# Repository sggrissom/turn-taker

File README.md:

# Turn Taker - RP2040 + SSD1315 OLED Project

A Raspberry Pi Pico project with SSD1315/SSD1306 I2C OLED display support.

## Prerequisites

1. **Pico SDK** - Install the Raspberry Pi Pico SDK:
   ```bash
   git clone https://github.com/raspberrypi/pico-sdk.git
   cd pico-sdk
   git submodule update --init
   export PICO_SDK_PATH=$(pwd)
   ```

2. **ARM Toolchain**:
   ```bash
   # Arch Linux
   sudo pacman -S arm-none-eabi-gcc arm-none-eabi-newlib

   # Ubuntu/Debian
   sudo apt install gcc-arm-none-eabi libnewlib-arm-none-eabi
   ```

3. **CMake** (version 3.13+):
   ```bash
   # Arch Linux
   sudo pacman -S cmake

   # Ubuntu/Debian
   sudo apt install cmake
   ```

## Wiring

Connect the SSD1315 OLED display to the Pico:

| Pico Pin | GPIO | Display Pin | Description  |
|----------|------|-------------|--------------|
| 6        | GP4  | SDA         | I2C Data     |
| 7        | GP5  | SCL         | I2C Clock    |
| 36       | 3V3  | VCC         | Power (3.3V) |
| 38       | GND  | GND         | Ground       |

```
         ┌─────────────────┐
         │  Raspberry Pi   │
         │      Pico       │
         │                 │
    SDA ─┤ GP4 (pin 6)     │
    SCL ─┤ GP5 (pin 7)     │
    VCC ─┤ 3V3 (pin 36)    │
    GND ─┤ GND (pin 38)    │
         └─────────────────┘
```

## Building

1. Set the SDK path (if not already set):
   ```bash
   export PICO_SDK_PATH=/path/to/pico-sdk
   ```

2. Create build directory and compile:
   ```bash
   mkdir build && cd build
   cmake ..
   make
   ```

3. The build produces `turn_taker.uf2` in the build directory.

## Flashing

1. Hold the **BOOTSEL** button on the Pico while connecting USB
2. The Pico will appear as a USB mass storage device (RPI-RP2)
3. Copy `turn_taker.uf2` to the device:
   ```bash
   cp build/turn_taker.uf2 /run/media/$USER/RPI-RP2/
   ```
4. The Pico will automatically reboot and run the program

## Configuration

Edit `include/config.h` to change:
- I2C pins (default: GP4/GP5)
- Display dimensions (default: 128x64)
- I2C address (default: 0x3C)

## Display Driver API

```c
// Initialize display
ssd1306_init(&display, I2C_PORT, addr, width, height);

// Clear buffer
ssd1306_clear(&display);

// Drawing functions
ssd1306_draw_pixel(&display, x, y, color);
ssd1306_draw_line(&display, x0, y0, x1, y1, color);
ssd1306_draw_rect(&display, x, y, w, h, color);
ssd1306_fill_rect(&display, x, y, w, h, color);
ssd1306_draw_char(&display, x, y, 'A', color);
ssd1306_draw_string(&display, x, y, "Hello", color);

// Send buffer to display
ssd1306_display(&display);

// Other controls
ssd1306_set_contrast(&display, 0xFF);
ssd1306_invert(&display, true);
```

## USB Serial Debug

The project is configured to output to USB serial. Connect via:
```bash
# Find the device
ls /dev/ttyACM*

# Connect (e.g., using minicom)
minicom -D /dev/ttyACM0 -b 115200
```

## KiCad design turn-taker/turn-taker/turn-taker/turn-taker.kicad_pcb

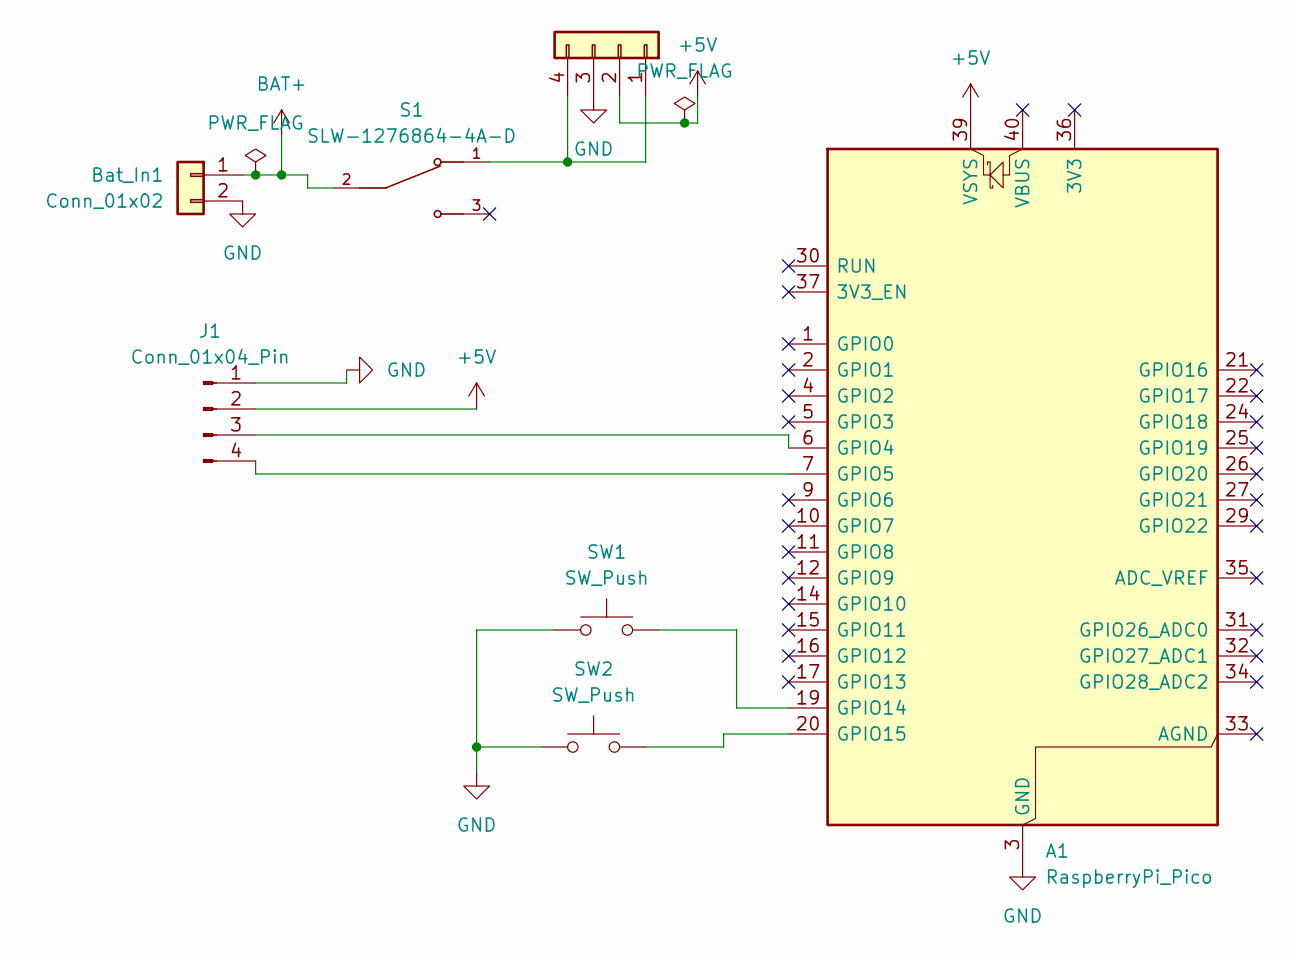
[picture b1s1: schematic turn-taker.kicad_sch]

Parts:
A1: RaspberryPi_Pico; RaspberryPi_Pico_Common_Unspecified
Bat_In1: Conn_01x02; JST_PH_S3B-PH-K_1x03_P2.00mm_Horizontal
J1: Conn_01x04_Pin; JST_PH_B4B-PH-K_1x04_P2.00mm_Vertical
J2: Conn_01x04; PinHeader_1x04_P2.54mm_Vertical
S1: SLW-1276864-4A-D; SW_SLW-1276864-4A-D; PARTREV 1.01
SW1, SW2: SW_Push; SW_PUSH_6mm

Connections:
+5V: A1.39 (VSYS), J1.2, J2.2
BAT+: Bat_In1.1, S1.2
GND: A1.3 (GND), A1.8 (GND), A1.13 (GND), A1.18 (GND), A1.23 (GND), A1.28 (GND), A1.38 (GND), Bat_In1.2, J1.1, J2.3, SW1.1, SW2.1
unnamed: A1.6 (GPIO4), J1.3
unnamed: A1.7 (GPIO5), J1.4
unnamed: A1.19 (GPIO14), SW1.2
unnamed: A1.20 (GPIO15), SW2.2
unnamed: J2.1, J2.4, S1.1

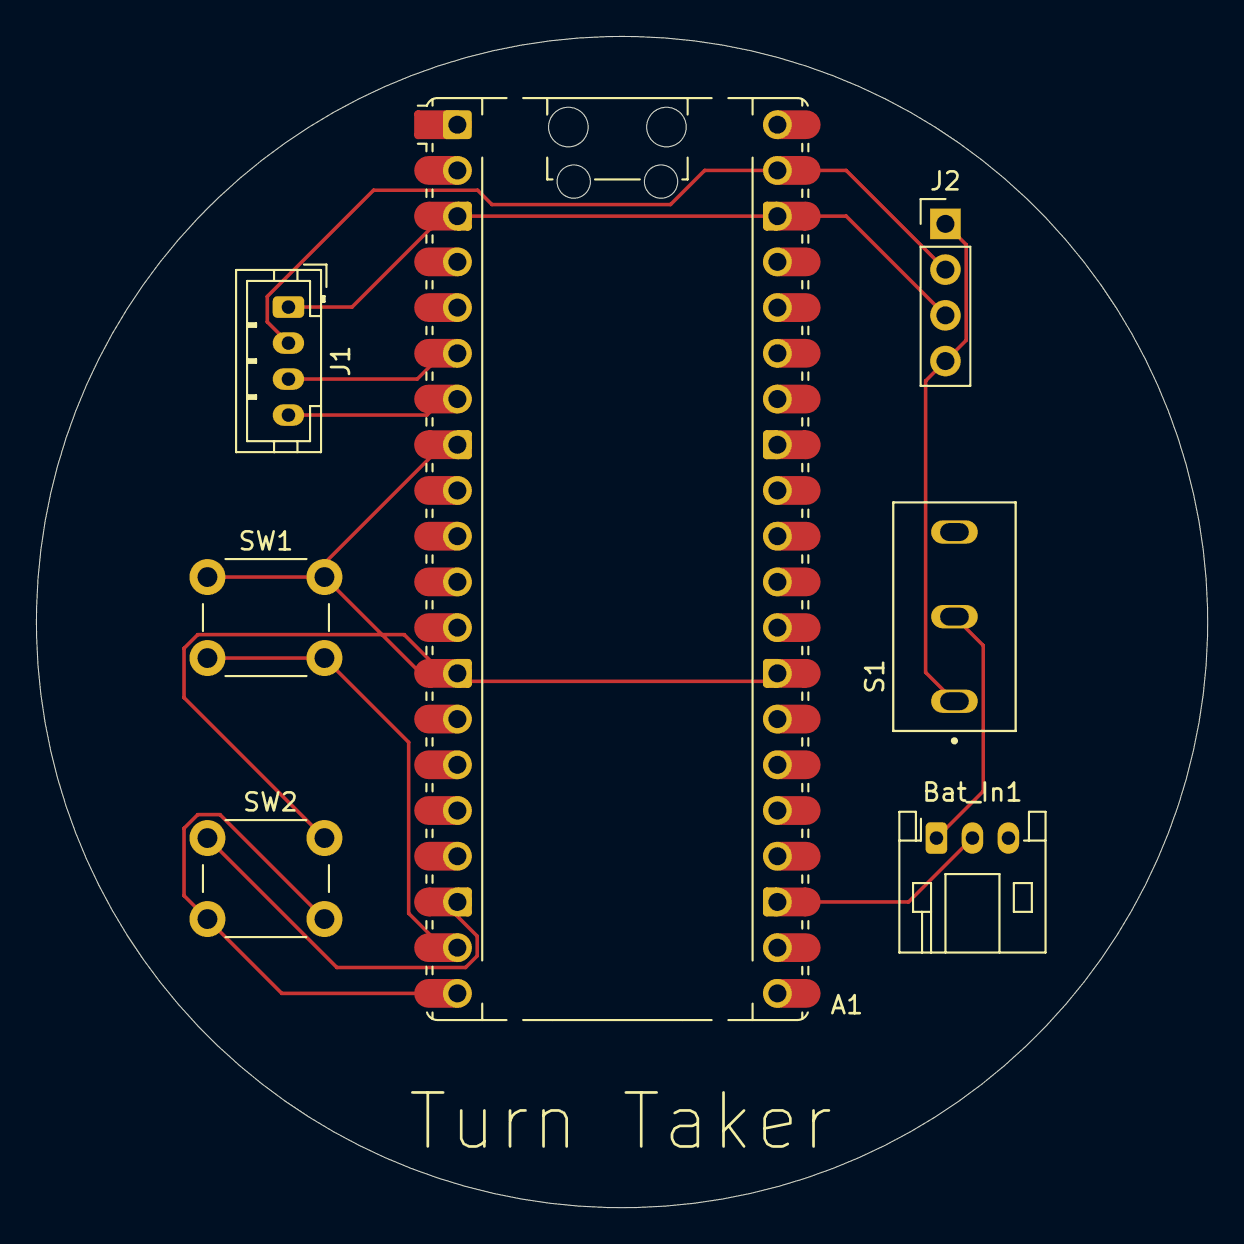
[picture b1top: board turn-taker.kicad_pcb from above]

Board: 2 copper layers, 65.1 x 65.1 mm, 7 parts (0 on the bottom side), 8 nets.

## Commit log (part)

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2025-11-30 repository setup for a simple rp2040 project
2025-11-30 switch to a unity build for the display library
2025-12-02 add simple button for hardware testing
2025-12-06 add a simple blink test to ensure I can deploy to the microprocessor
2025-12-06 hello world is working on the screen now
2025-12-06 toggle between showing names, and have them scaled up to appear bigger
2025-12-06 show dots for a person's turn count
2025-12-06 add a "defer" button
2025-12-06 add some ui polish. animation, high contrast, some border lines
2025-12-06 add persistent storage
2025-12-07 adding kicad files, just started the schematic
2025-12-08 schematic fixes
2025-12-14 finshed the schematic with footprints
2025-12-14 laid out the board
2025-12-14 generated gerber and drill files, v1
2025-12-15 fixed the switch type in the schematic to match the part
2025-12-15 update pcb with correct switch footprint
2025-12-16 update the jst connector for the screen in the schematic, footprint, and the pcb
2025-12-16 update the gerber and drill files
2025-12-16 update the zip file
2025-12-27 add buttons testing to the deployment test
2025-12-29 generate step file for 3d model
2025-12-29 cad project start, pcb model imported
2026-02-05 simple ring 3d model
2026-02-05 adding a floor to the model
2026-02-06 3d model with constraints
